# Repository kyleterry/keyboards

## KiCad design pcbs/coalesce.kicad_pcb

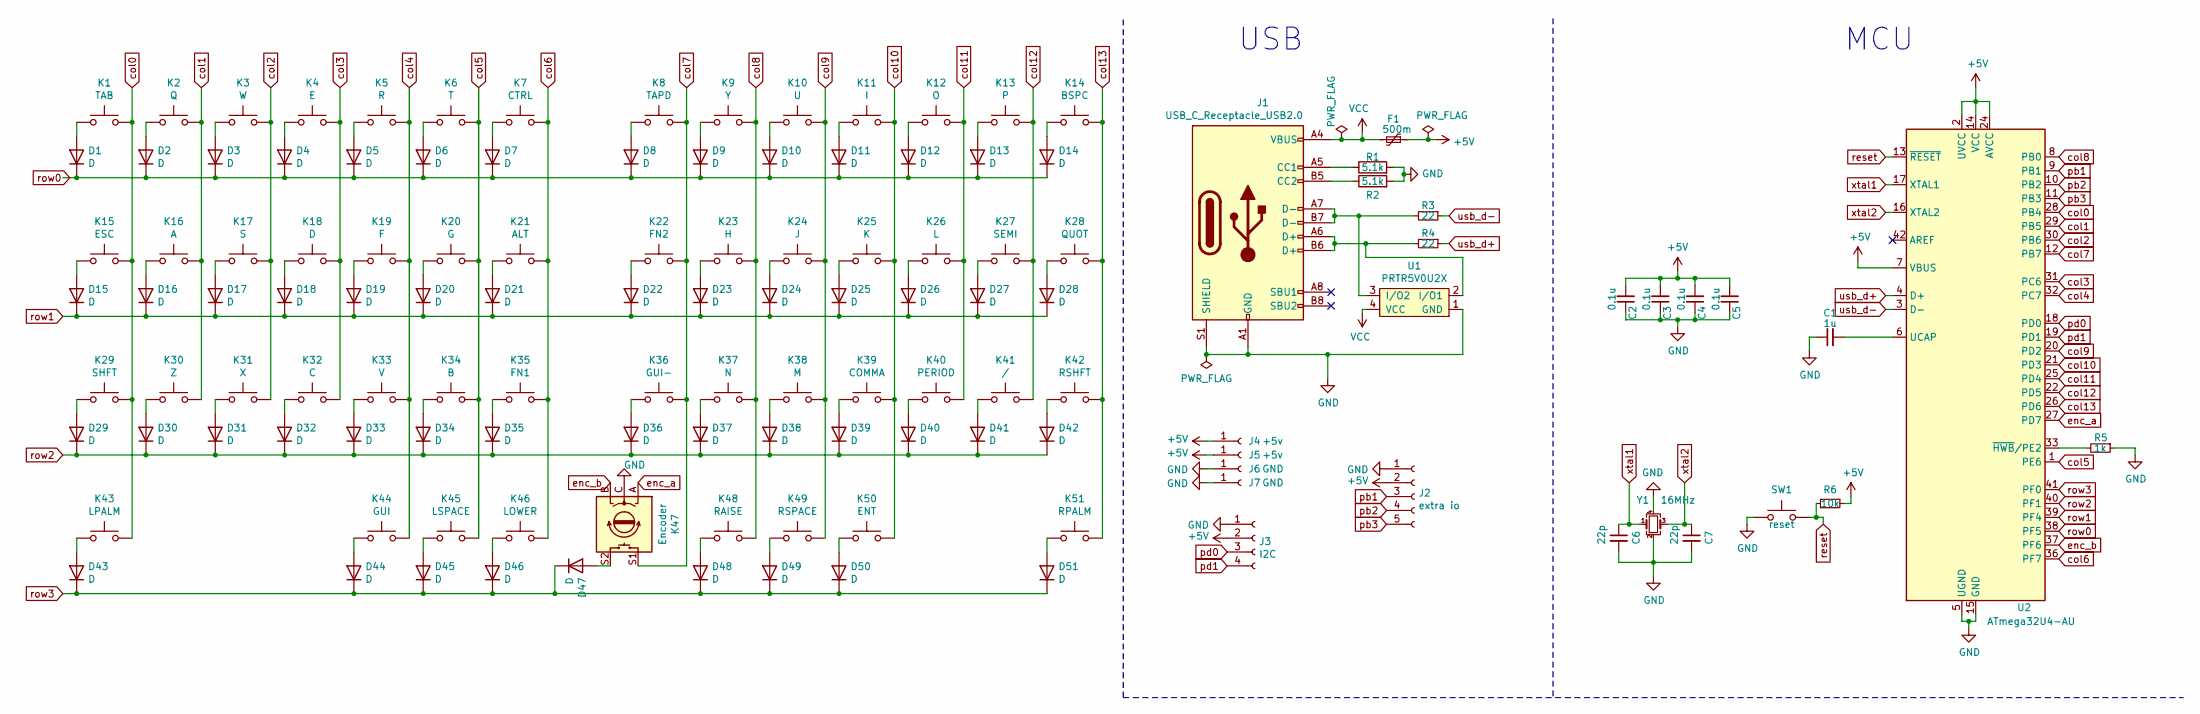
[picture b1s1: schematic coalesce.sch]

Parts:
C1: 1u; C_0805_2012Metric_Pad1.15x1.40mm_HandSolder
C2, C3, C4, C5: 0.1u; C_0805_2012Metric_Pad1.15x1.40mm_HandSolder
C6, C7: 22p; C_0805_2012Metric_Pad1.15x1.40mm_HandSolder
D1, D2, D3, D4, D5, D6, D7, D8, D9, D10, D11, D12, D13, D14, D15, D16, D17, D18, D19, D20, D21, D22, D23, D24, D25, D26, D27, D28, D29, D30, D31, D32, D33, D34, D35, D36, D37, D38, D39, D40, D41, D42, D43, D44, D45, D46, D47, D48, D49, D50, D51: D; D_SOD123_axial
F1: 500m; Fuse_1206_3216Metric_Pad1.42x1.75mm_HandSolder
J1: USB_C_Receptacle_USB2.0; USB_C_Receptacle_HRO_TYPE-C-31-M-12
J2: extra io; 1X05_NO_SILK
J3: I2C; 1X04_NO_SILK
J4, J5: +5v; 1X01_NO_SILK
J6, J7: GND; 1X01_NO_SILK
K1: TAB; Mx-Alps-1U
K2: Q; Mx-Alps-1U
K3: W; Mx-Alps-1U
K4: E; Mx-Alps-1U
K5: R; Mx-Alps-1U
K6: T; Mx-Alps-1U
K7: CTRL; Mx-Alps-1U
K8: TAPD; Mx-Alps-1U
K9: Y; Mx-Alps-1U
K10: U; Mx-Alps-1U
K11: I; Mx-Alps-1U
K12: O; Mx-Alps-1U
K13: P; Mx-Alps-1U
K14: BSPC; Mx-Alps-1U
K15: ESC; Mx-Alps-1U
K16: A; Mx-Alps-1U
K17: S; Mx-Alps-1U
K18: D; Mx-Alps-1U
K19: F; Mx-Alps-1U
K20: G; Mx-Alps-1U
K21: ALT; Mx-Alps-1U
K22: FN2; Mx-Alps-1U
K23: H; Mx-Alps-1U
K24: J; Mx-Alps-1U
K25: K; Mx-Alps-1U
K26: L; Mx-Alps-1U
K27: SEMI; Mx-Alps-1U
K28: QUOT; Mx-Alps-1U
K29: SHFT; Mx-Alps-1U
K30: Z; Mx-Alps-1U
K31: X; Mx-Alps-1U
K32: C; Mx-Alps-1U
K33: V; Mx-Alps-1U
K34: B; Mx-Alps-1U
K35: FN1; Mx-Alps-1U
K36: GUI-; Mx-Alps-1U
K37: N; Mx-Alps-1U
K38: M; Mx-Alps-1U
K39: COMMA; Mx-Alps-1U
K40: PERIOD; Mx-Alps-1U
K41: /; Mx-Alps-1U
K42: RSHFT; Mx-Alps-1U
K43: LPALM; Mx-Alps-1U
K44: GUI; Mx-Alps-1U
K45: LSPACE; Mx-Alps-vertical-125U
K46: LOWER; Mx-Alps-vertical-175U
K47: Encoder; RotaryEncoder_Alps_EC11E-Switch_Vertical_H20mm
K48: RAISE; Mx-Alps-vertical-175U
K49: RSPACE; Mx-Alps-vertical-125U
K50: ENT; Mx-Alps-1U
K51: RPALM; Mx-Alps-1U
R1, R2: 5.1k; R_0805_2012Metric_Pad1.15x1.40mm_HandSolder
R3, R4: 22; R_0805_2012Metric_Pad1.15x1.40mm_HandSolder
R5: 1k; R_0805_2012Metric_Pad1.15x1.40mm_HandSolder
R6: 10k; R_0805_2012Metric_Pad1.15x1.40mm_HandSolder
SW1: reset; TACTILE_SWITCH_SMD_4.6X2.8MM
U1: PRTR5V0U2X; SOT-143B
U2: ATmega32U4-AU; TQFP-44_10x10mm_Pitch0.8mm
Y1: 16MHz; Crystal_SMD_SeikoEpson_FA238-4Pin_3.2x2.5mm_HandSoldering

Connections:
+5V: C2.2, C3.2, C4.2, C5.2, F1.1, J2.2, J3.2, J4.1, J5.1, R6.1, U2.2 (UVCC), U2.7 (VBUS), U2.14 (VCC), U2.24 (AVCC), U2.34 (VCC), U2.44 (AVCC)
GND: C1.1, C2.1, C3.1, C4.1, C5.1, C6.2, C7.2, J1.A1 (GND), J1.A12 (GND), J1.B1 (GND), J1.B12 (GND), J1.S1 (SHIELD), J2.1, J3.1, J6.1, J7.1, K47.C, R1.2, R2.2, R5.1, SW1.1, U1.1 (GND), U2.5 (UGND), U2.15 (GND), U2.23 (GND), U2.35 (GND), U2.43 (GND), Y1.2, Y1.4
unnamed: C1.2, U2.6 (UCAP)
unnamed: D1.2 (A), K1.1
unnamed: D2.2 (A), K2.1
unnamed: D3.2 (A), K3.1
unnamed: D4.2 (A), K4.1
unnamed: D5.2 (A), K5.1
unnamed: D6.2 (A), K6.1
unnamed: D7.2 (A), K7.1
unnamed: D8.2 (A), K8.1
unnamed: D9.2 (A), K9.1
unnamed: D10.2 (A), K10.1
unnamed: D11.2 (A), K11.1
unnamed: D12.2 (A), K12.1
unnamed: D13.2 (A), K13.1
unnamed: D14.2 (A), K14.1
unnamed: D15.2 (A), K15.1
unnamed: D16.2 (A), K16.1
unnamed: D17.2 (A), K17.1
unnamed: D18.2 (A), K18.1
unnamed: D19.2 (A), K19.1
unnamed: D20.2 (A), K20.1
unnamed: D21.2 (A), K21.1
unnamed: D22.2 (A), K22.1
unnamed: D23.2 (A), K23.1
unnamed: D24.2 (A), K24.1
unnamed: D25.2 (A), K25.1
unnamed: D26.2 (A), K26.1
unnamed: D27.2 (A), K27.1
unnamed: D28.2 (A), K28.1
unnamed: D29.2 (A), K29.1
unnamed: D30.2 (A), K30.1
unnamed: D31.2 (A), K31.1
unnamed: D32.2 (A), K32.1
unnamed: D33.2 (A), K33.1
unnamed: D34.2 (A), K34.1
unnamed: D35.2 (A), K35.1
unnamed: D36.2 (A), K36.1
unnamed: D37.2 (A), K37.1
unnamed: D38.2 (A), K38.1
unnamed: D39.2 (A), K39.1
unnamed: D40.2 (A), K40.1
unnamed: D41.2 (A), K41.1
unnamed: D42.2 (A), K42.1
unnamed: D43.2 (A), K43.1
unnamed: D44.2 (A), K44.1
unnamed: D45.2 (A), K45.1
unnamed: D46.2 (A), K46.1
unnamed: D47.2 (A), K47.S2
unnamed: D48.2 (A), K48.1
unnamed: D49.2 (A), K49.1
unnamed: D50.2 (A), K50.1
unnamed: D51.2 (A), K51.1
unnamed: J1.A5 (CC1), R1.1
unnamed: J1.A6 (D+), J1.B6 (D+), R4.2, U1.2 (I/O1)
unnamed: J1.A7 (D-), J1.B7 (D-), R3.2, U1.3 (I/O2)
unnamed: J1.B5 (CC2), R2.1
unnamed: R5.2, U2.33 (~HWB~/PE2)
VCC: F1.2, J1.A4 (VBUS), J1.A9 (VBUS), J1.B4 (VBUS), J1.B9 (VBUS), U1.4 (VCC)
col0: K1.2, K15.2, K29.2, K43.2, U2.28 (PB4)
col1: K2.2, K16.2, K30.2, U2.29 (PB5)
col2: K3.2, K17.2, K31.2, U2.30 (PB6)
col3: K4.2, K18.2, K32.2, U2.31 (PC6)
col4: K5.2, K19.2, K33.2, K44.2, U2.32 (PC7)
col5: K6.2, K20.2, K34.2, K45.2, U2.1 (PE6)
col6: K7.2, K21.2, K35.2, K46.2, U2.36 (PF7)
col7: K8.2, K22.2, K36.2, K47.S1, U2.12 (PB7)
col8: K9.2, K23.2, K37.2, K48.2, U2.8 (PB0)
col9: K10.2, K24.2, K38.2, K49.2, U2.20 (PD2)
col10: K11.2, K25.2, K39.2, K50.2, U2.21 (PD3)
col11: K12.2, K26.2, K40.2, U2.25 (PD4)
col12: K13.2, K27.2, K41.2, U2.22 (PD5)
col13: K14.2, K28.2, K42.2, K51.2, U2.26 (PD6)
enc_a: K47.A, U2.27 (PD7)
enc_b: K47.B, U2.37 (PF6)
pb1: J2.3, U2.9 (PB1)
pb2: J2.4, U2.10 (PB2)
pb3: J2.5, U2.11 (PB3)
pd0: J3.3, U2.18 (PD0)
pd1: J3.4, U2.19 (PD1)
reset: R6.2, SW1.2, U2.13 (~RESET)
row0: D1.1 (K), D2.1 (K), D3.1 (K), D4.1 (K), D5.1 (K), D6.1 (K), D7.1 (K), D8.1 (K), D9.1 (K), D10.1 (K), D11.1 (K), D12.1 (K), D13.1 (K), D14.1 (K), U2.38 (PF5)
row1: D15.1 (K), D16.1 (K), D17.1 (K), D18.1 (K), D19.1 (K), D20.1 (K), D21.1 (K), D22.1 (K), D23.1 (K), D24.1 (K), D25.1 (K), D26.1 (K), D27.1 (K), D28.1 (K), U2.39 (PF4)
row2: D29.1 (K), D30.1 (K), D31.1 (K), D32.1 (K), D33.1 (K), D34.1 (K), D35.1 (K), D36.1 (K), D37.1 (K), D38.1 (K), D39.1 (K), D40.1 (K), D41.1 (K), D42.1 (K), U2.40 (PF1)
row3: D43.1 (K), D44.1 (K), D45.1 (K), D46.1 (K), D47.1 (K), D48.1 (K), D49.1 (K), D50.1 (K), D51.1 (K), U2.41 (PF0)
usb_d+: R4.1, U2.4 (D+)
usb_d-: R3.1, U2.3 (D-)
xtal1: C6.1, U2.17 (XTAL1), Y1.1
xtal2: C7.1, U2.16 (XTAL2), Y1.3

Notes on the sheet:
MCU
USB

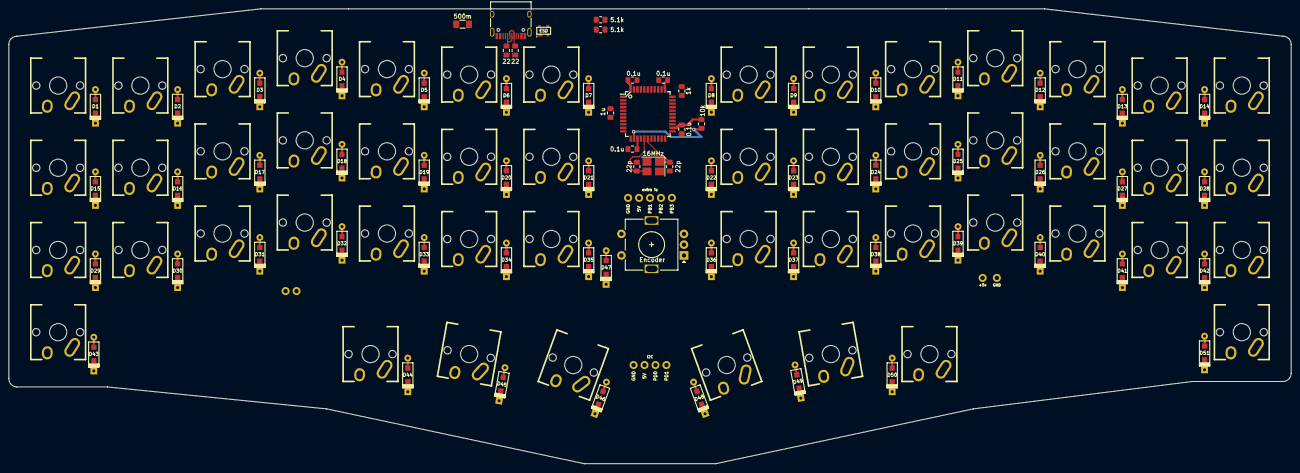
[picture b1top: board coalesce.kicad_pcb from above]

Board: 2 copper layers, 297.2 x 105.4 mm, 127 parts (1 on the bottom side), 90 nets.

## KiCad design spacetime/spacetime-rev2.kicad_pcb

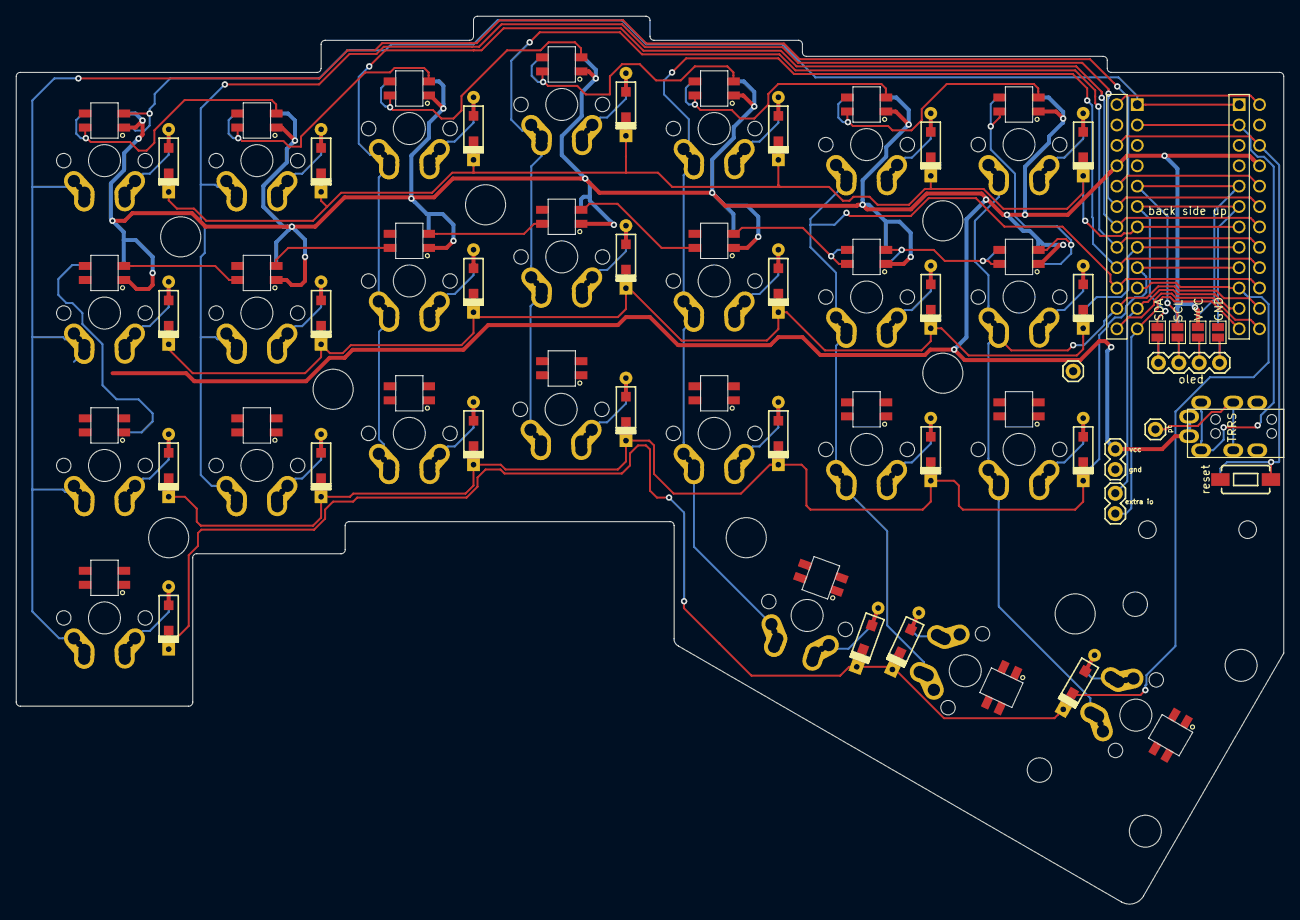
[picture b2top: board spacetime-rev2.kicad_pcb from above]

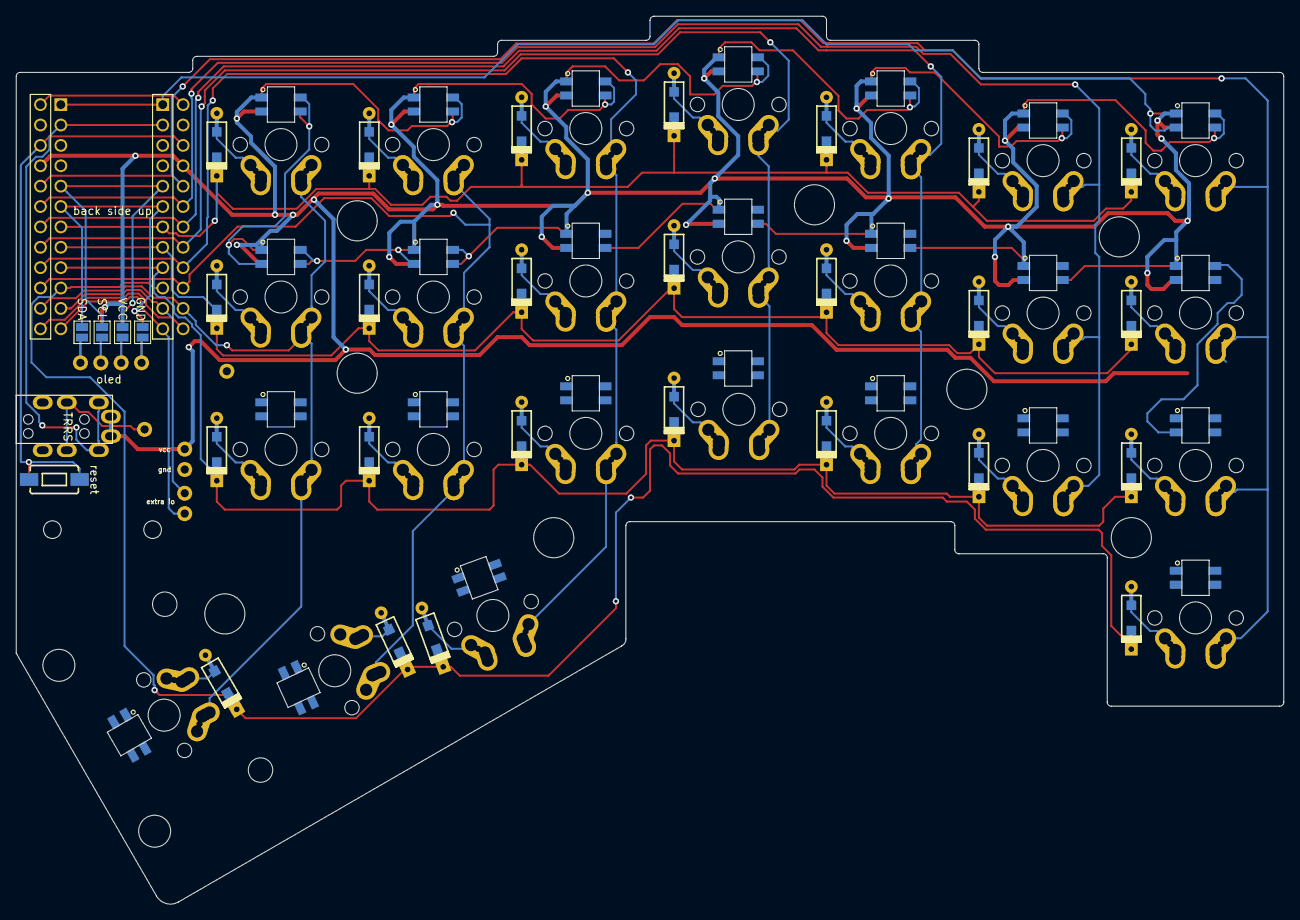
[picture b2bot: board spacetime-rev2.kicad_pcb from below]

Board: 2 copper layers, 158.0 x 110.7 mm, 92 parts (5 on the bottom side), 75 nets.

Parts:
>NAME: >VALUE; 1X02
D1, D2, D3, D4, D5, D6, D7, D8, D9, D10, D11, D12, D13, D14, D15, D16, D17, D18, D19, D20, D21, D22, D23, D24, D25: D; D_SOD123_axial_reversible
GND: SOLDER_JUMPER; SolderJumper-2_P1.3mm_Open_Pad1.0x1.5mm
GND#2: SOLDER_JUMPER; SolderJumper-2_P1.3mm_Open_Pad1.0x1.5mm
J2: pt; 1X01
J3: TRRS; trrs
J4: OLED; 1X04
J7: extra io; 1X02
J8: CONN_01; 1X01
K1, K2, K3, K4, K5, K6, K7, K8, K9, K10, K11, K12, K13, K14, K15, K16, K17, K18, K19, K20, K21, K22, K23: KEYSW; Hybrid_PCB_100H_Dual_hole-nosilk
K24: KEYSW; Hybrid_PCB_125H_Dual_hole-nosilk
K25: KEYSW; Hybrid_PCB_200H-dual-nosilk
L1, L2, L3, L4, L5, L6, L7, L8, L9, L10, L11, L12, L13, L14, L15, L16, L17, L18, L19, L20, L21, L22, L23, L24, L25: SK6812MINI
SCL: SOLDER_JUMPER; SolderJumper-2_P1.3mm_Open_Pad1.0x1.5mm
SCL#2: SOLDER_JUMPER; SolderJumper-2_P1.3mm_Open_Pad1.0x1.5mm
SDA: SOLDER_JUMPER; SolderJumper-2_P1.3mm_Open_Pad1.0x1.5mm
SDA#2: SOLDER_JUMPER; SolderJumper-2_P1.3mm_Open_Pad1.0x1.5mm
U1: ProMicro; ProMicro-reversible
VCC: SOLDER_JUMPER; SolderJumper-2_P1.3mm_Open_Pad1.0x1.5mm
VCC#2: SOLDER_JUMPER; SolderJumper-2_P1.3mm_Open_Pad1.0x1.5mm
reset: RESET BTN; TACTILE_SWITCH_SMD_6.0X3.5MM
reset#2: RESET BTN; TACTILE_SWITCH_SMD_6.0X3.5MM

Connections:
/col0: K1.1, K8.1, K15.1, K22.1, U1.20
/col1: K2.1, K9.1, K16.1, U1.19
/col2: K3.1, K10.1, K17.1, U1.18
/col3: K4.1, K11.1, K18.1, U1.17
/col4: K5.1, K12.1, K19.1, K23.1, U1.16
/col5: K6.1, K13.1, K20.1, K24.1, U1.15
/col6: K7.1, K14.1, K21.1, K25.1, U1.14
/led: L1.3, U1.1
/pt0: J2.1, J3.C
/row0: D1.1, D2.1, D3.1, D4.1, D5.1, D6.1, D7.1, U1.7
/row1: D8.1, D9.1, D10.1, D11.1, D12.1, D13.1, D14.1, U1.8
/row2: D15.1, D16.1, D17.1, D18.1, D19.1, D20.1, D21.1, U1.9
/row3: D22.1, D23.1, D24.1, D25.1, U1.10
/rst: U1.22, reset.1, reset#2.1
/scl: SCL.2, SCL#2.2, U1.5
/sda: SDA.2, SDA#2.2, U1.6
/serial: J3.D, U1.2
/xd0: J8.1, U1.13
GND: >NAME.1, GND.2, GND#2.2, J3.B, L1.2, L2.2, L3.2, L4.2, L5.2, L6.2, L7.2, L8.2, L9.2, L10.2, L11.2, L12.2, L13.2, L14.2, L15.2, L16.2, L17.2, L18.2, L19.2, L20.2, L21.2, L22.2, L23.2, L24.2, L25.2, U1.3, U1.4, U1.23, reset.2, reset#2.2
unnamed: D1.2, K1.2
unnamed: D2.2, K2.2
unnamed: D3.2, K3.2
unnamed: D4.2, K4.2
unnamed: D5.2, K5.2
unnamed: D6.2, K6.2
unnamed: D7.2, K7.2
unnamed: D8.2, K8.2
unnamed: D9.2, K9.2
unnamed: D10.2, K10.2
unnamed: D11.2, K11.2
unnamed: D12.2, K12.2
unnamed: D13.2, K13.2
unnamed: D14.2, K14.2
unnamed: D15.2, K15.2
unnamed: D16.2, K16.2
unnamed: D17.2, K17.2
unnamed: D18.2, K18.2
unnamed: D19.2, K19.2
unnamed: D20.2, K20.2
unnamed: D21.2, K21.2
unnamed: D22.2, K22.2
unnamed: D23.2, K23.2
unnamed: D24.2, K24.2
unnamed: D25.2, K25.2
unnamed: GND.1, J4.1, SDA#2.1
unnamed: J4.2, SCL#2.1, VCC.1
unnamed: J4.3, SCL.1, VCC#2.1
unnamed: GND#2.1, J4.4, SDA.1
unnamed: J7.1, U1.12
unnamed: J7.2, U1.11
unnamed: L1.1, L2.3
unnamed: L2.1, L3.3
unnamed: L3.1, L4.3
unnamed: L4.1, L5.3
unnamed: L5.1, L6.3
unnamed: L6.1, L7.3
unnamed: L8.3, L9.1
unnamed: L9.3, L10.1
unnamed: L10.3, L11.1
unnamed: L11.3, L12.1
unnamed: L12.3, L13.1
unnamed: L13.3, L14.1
unnamed: L7.1, L14.3
unnamed: L15.1, L16.3
unnamed: L8.1, L15.3
unnamed: L16.1, L17.3
unnamed: L17.1, L18.3
unnamed: L18.1, L19.3
unnamed: L19.1, L20.3
unnamed: L20.1, L21.3
unnamed: L21.1, L25.3
unnamed: L22.3, L23.1
unnamed: L23.3, L24.1
unnamed: L24.3, L25.1
VCC: >NAME.2, J3.A, L1.4, L2.4, L3.4, L4.4, L5.4, L6.4, L7.4, L8.4, L9.4, L10.4, L11.4, L12.4, L13.4, L14.4, L15.4, L16.4, L17.4, L18.4, L19.4, L20.4, L21.4, L22.4, L23.4, L24.4, L25.4, U1.21, VCC.2, VCC#2.2

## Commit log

2020-10-05 adds coalesce pcb
